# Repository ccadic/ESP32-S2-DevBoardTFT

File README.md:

# ESP32-S2-DevBoardTFT

BREAKING NEWS !!!!! We started a Crowdsupply campaign because of many requests. You can get a fully assembled product here: https://www.crowdsupply.com/morpheans/morphesp-240

Esp32-S2 dev board with 240x240 IPS display

A powerfull dev board with the ESPRESSIF™ ESP32-S2®, a high resolution display, a RGB LED, a battery charger and a bunch of GPIOs.

There are many ESP32 board on the market but very few with the new ESP32-S2 which handles USB communications, new cryptography functions. We wanted to have a board with a built in hi-resolution IPS Color Display. After years playing with previous versions of the ESP32, building security devices, text pagers, we just wanted to go one step further and have our opensource circuit.

We wanted to have something minimalistic but expandable so we chose the ESP32 S2 WROOM component , a classic WS2812B RGB LED, a classic 5v to 3.V voltage regulator. 
We wanted something extremely easy to use therefore fully compatible with ARDUINO® IDE plateform.  We also wanted something simple to handle as a first crowdfunding project. 

Features & Specifications

•	Processing:
    o	32-bit esp32 processor operating at 240 MHz
    o	4 MB SPI flash

•	Wireless:
    o	2.4 GHz Wi-Fi - 802.11b/g/n
    o	PCB Antenna

•	Power:
    o	3.3 V LDO regulator
    o	Optimised power path for low-power battery usage
    o	LiPo battery management
    o	Battery pads on the bottom support both JST PH 
    o	Power LEDs

•	Form-factor:
    o	1.27 pinout spacing connector
    o	Breadboard friendly with the dev shield

•	Connectivity:
    o	GPIO broken out to standard pitch headers 1.27 mm
    o	USB + serial/UART for programming
    o	On Board Programmable RGB LED

•	Control:
    o	Arduino IDE compatibility and MicroPython compatibilité
    o	Supports Arduino IDE
    o	Supports Espressif IDF
    o	Thousands of code over the internet

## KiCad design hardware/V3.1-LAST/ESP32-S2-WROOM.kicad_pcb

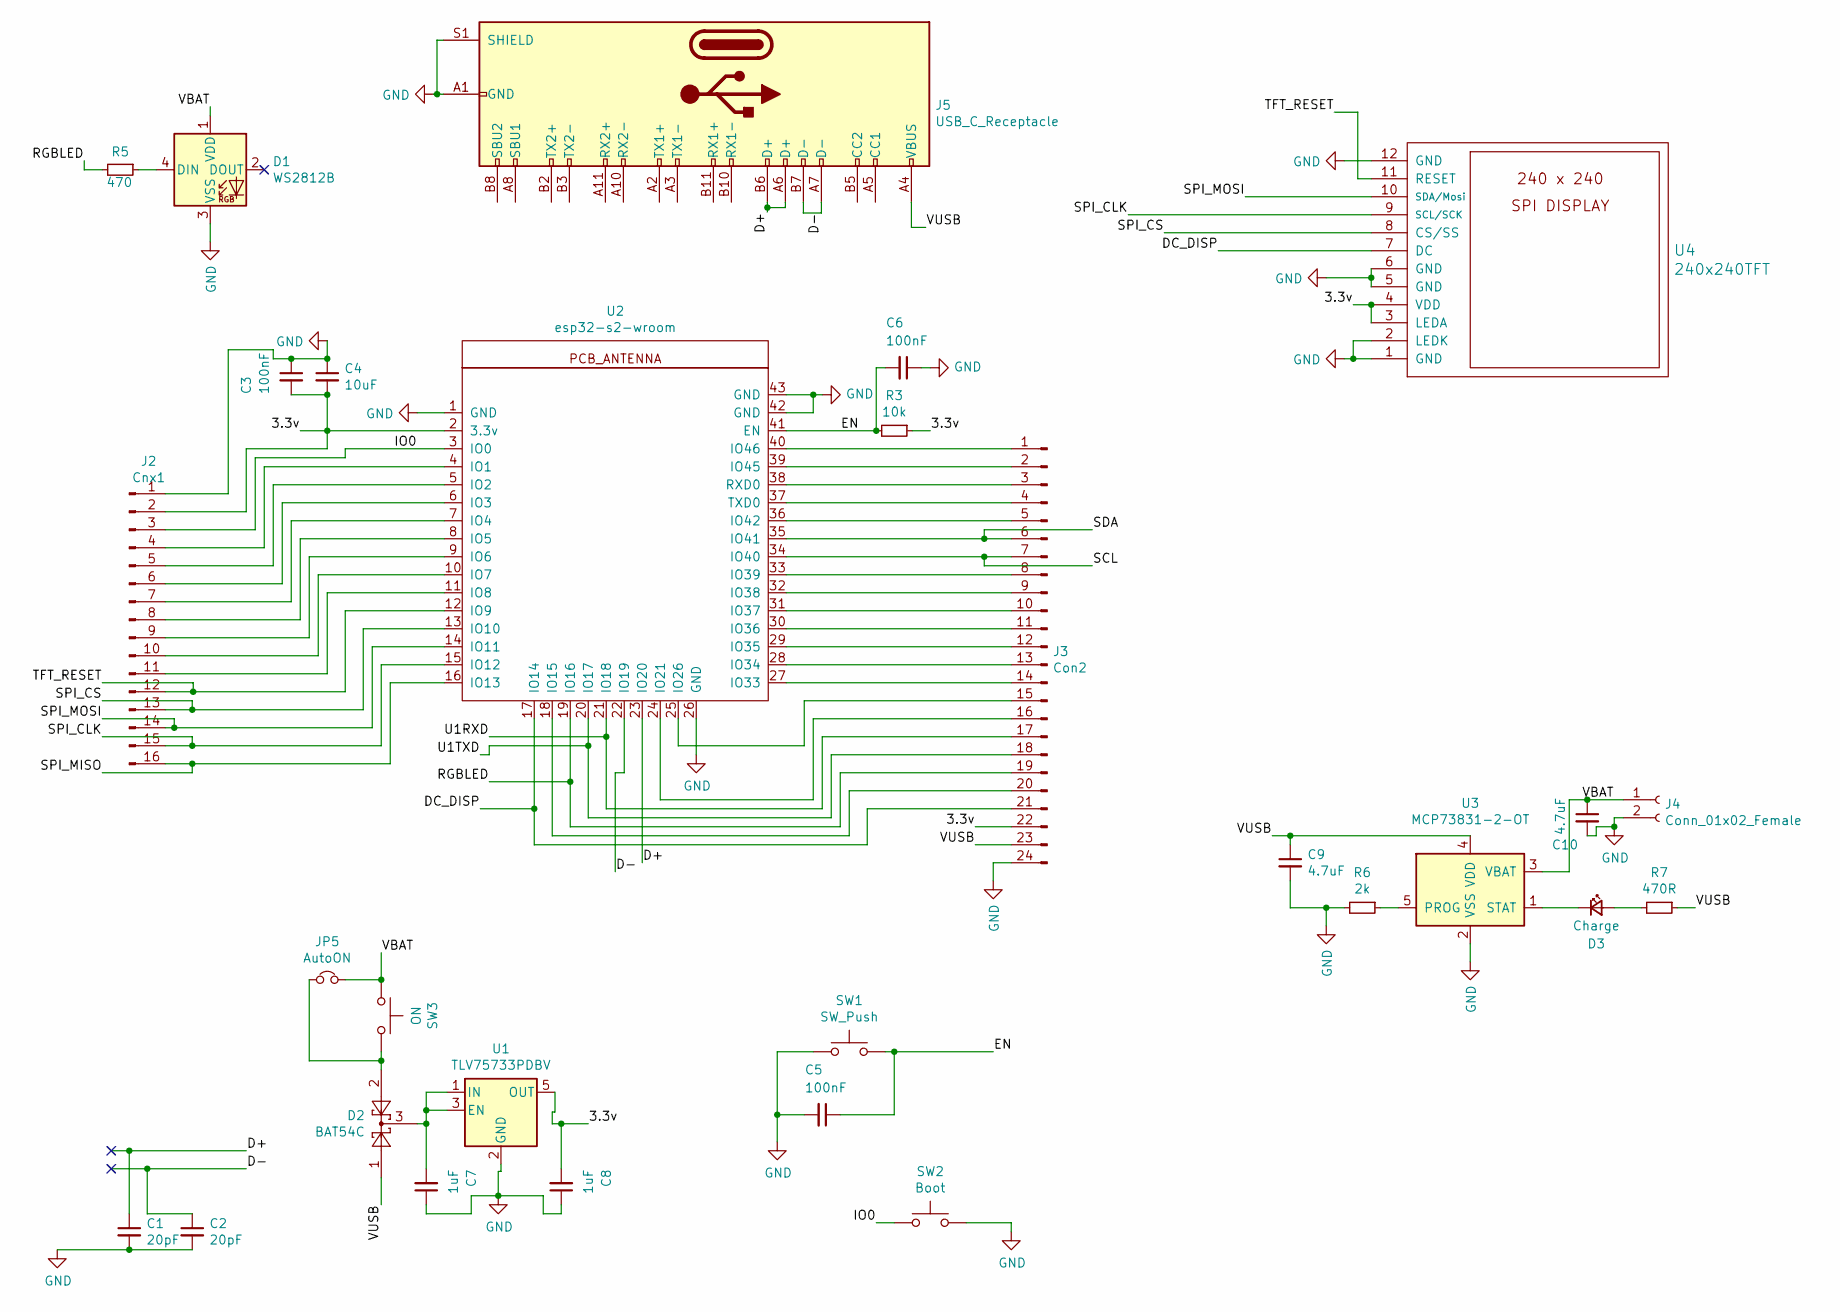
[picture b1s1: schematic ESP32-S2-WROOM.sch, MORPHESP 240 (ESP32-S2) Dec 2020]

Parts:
C1, C2: 20pF; C_0603
C3, C5, C6: 100nF; C_0603
C4: 10uF; C_0603
C7, C8: 1uF; C_0603
C9, C10: 4.7uF; C_0603
D1: WS2812B; LED_WS2812B-PLCC4
D2: BAT54C; SOT-23
D3: Charge; LED_0603
J2: Cnx1; Socket_Strip_Straight_1x16_Pitch1.27mm
J3: Con2; Socket_Strip_Straight_1x24_Pitch1.27mm
J4: Conn_01x02_Female; JST_PH_S2B-PH-SM4-TB_02x2.00mm_Angled
J5: USB_C_Receptacle; USB_C_Receptacle_GT-USB-7010
JP5: AutoON; JumperSmall
R3: 10k; R_0603
R5: 470; R_0603
R6: 2k; R_0603
R7: 470R; R_0603
SW1: SW_Push; SW_SPST_B3U-1000P
SW2: Boot; SW_SPST_B3U-1000P
SW3: ON; SW_SPDT_PCM12
U1: TLV75733PDBV; SOT-23-5
U2: esp32-s2-wroom; esp32-s2-wrooom
U3: MCP73831-2-OT; SOT-23-5
U4: 240x240TFT; 240240TFT

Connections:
/3.3v: C3.2, C4.2, C8.2, J2.2, J3.22, R3.1, U1.5 (OUT), U2.2 (3.3v), U4.3 (LEDA), U4.4 (VDD)
/D+: C1.1, J5.A6 (D+), J5.B6 (D+), U2.23 (IO20)
/D-: C2.1, J5.A7 (D-), J5.B7 (D-), U2.22 (IO19)
/DC_DISP: J3.21, U2.17 (IO14), U4.7 (DC)
/EN: C5.1, C6.2, R3.2, SW1.2, U2.41 (EN)
/IO0: J2.3, SW2.1, U2.3 (IO0)
/RGBLED: J3.19, R5.2, U2.19 (IO16)
/SCL: J3.7, U2.34 (IO40)
/SDA: J3.6, U2.35 (IO41)
/SPI_CLK: J2.15, U2.15 (IO12), U4.9 (SCL/SCK)
/SPI_CS: J2.13, U2.13 (IO10), U4.8 (CS/SS)
/SPI_MISO: J2.16, U2.16 (IO13)
/SPI_MOSI: J2.14, U2.14 (IO11), U4.10 (SDA/Mosi)
/TFT_RESET: J2.12, U2.12 (IO9), U4.11 (RESET)
/U1RXD: J3.17, U2.21 (IO18)
/U1TXD: J3.18, U2.20 (IO17)
/VBAT: C10.1, D1.1 (VDD), J4.1, JP5.2, SW3.1, U3.3 (VBAT)
/VUSB: C9.1, D2.1, J3.23, J5.A4 (VBUS), J5.A9 (VBUS), J5.B4 (VBUS), J5.B9 (VBUS), R7.1, U3.4 (VDD)
GND: C1.2, C2.2, C3.1, C4.1, C5.2, C6.1, C7.1, C8.1, C9.2, C10.2, D1.3 (VSS), J2.1, J3.24, J4.2, J5.A1 (GND), J5.A12 (GND), J5.B1 (GND), J5.B12 (GND), J5.S1 (SHIELD), R6.2, SW1.1, SW2.2, U1.2 (GND), U2.1 (GND), U2.26 (GND), U2.42 (GND), U2.43 (GND), U3.2 (VSS), U4.1 (GND), U4.2 (LEDK), U4.5 (GND), U4.6 (GND), U4.12 (GND)
unnamed: C7.2, D2.3, U1.1 (IN), U1.3 (EN)
unnamed: D1.4 (DIN), R5.1
unnamed: D2.2, JP5.1, SW3.2
unnamed: D3.1 (K), U3.1 (STAT)
unnamed: D3.2 (A), R7.2
unnamed: J2.4, U2.4 (IO1)
unnamed: J2.5, U2.5 (IO2)
unnamed: J2.6, U2.6 (IO3)
unnamed: J2.7, U2.7 (IO4)
unnamed: J2.8, U2.8 (IO5)
unnamed: J2.9, U2.9 (IO6)
unnamed: J2.10, U2.10 (IO7)
unnamed: J2.11, U2.11 (IO8)
unnamed: J3.1, U2.40 (IO46)
unnamed: J3.2, U2.39 (IO45)
unnamed: J3.3, U2.38 (RXD0)
unnamed: J3.4, U2.37 (TXD0)
unnamed: J3.5, U2.36 (IO42)
unnamed: J3.8, U2.33 (IO39)
unnamed: J3.9, U2.32 (IO38)
unnamed: J3.10, U2.31 (IO37)
unnamed: J3.11, U2.30 (IO36)
unnamed: J3.12, U2.29 (IO35)
unnamed: J3.13, U2.28 (IO34)
unnamed: J3.14, U2.27 (IO33)
unnamed: J3.15, U2.25 (IO26)
unnamed: J3.16, U2.24 (IO21)
unnamed: J3.20, U2.18 (IO15)
unnamed: R6.1, U3.5 (PROG)

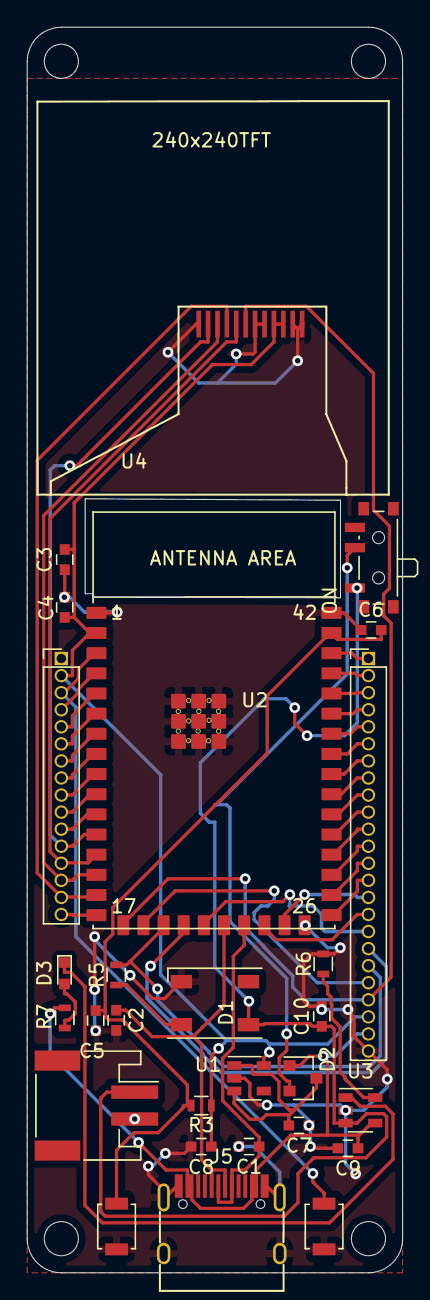
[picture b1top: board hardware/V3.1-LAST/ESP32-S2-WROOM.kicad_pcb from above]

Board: 2 copper layers, 27.9 x 92.7 mm, 29 parts (1 on the bottom side), 48 nets.

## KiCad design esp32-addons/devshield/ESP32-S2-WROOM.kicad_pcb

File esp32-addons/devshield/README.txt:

(C) 2020 - Dr CADIC Philippe
www.morpheans.com

This is a breadboard friendly development shield for the MORPHESP 240
You get access to all GPIO, grouped connectors (SPI , I2C)...

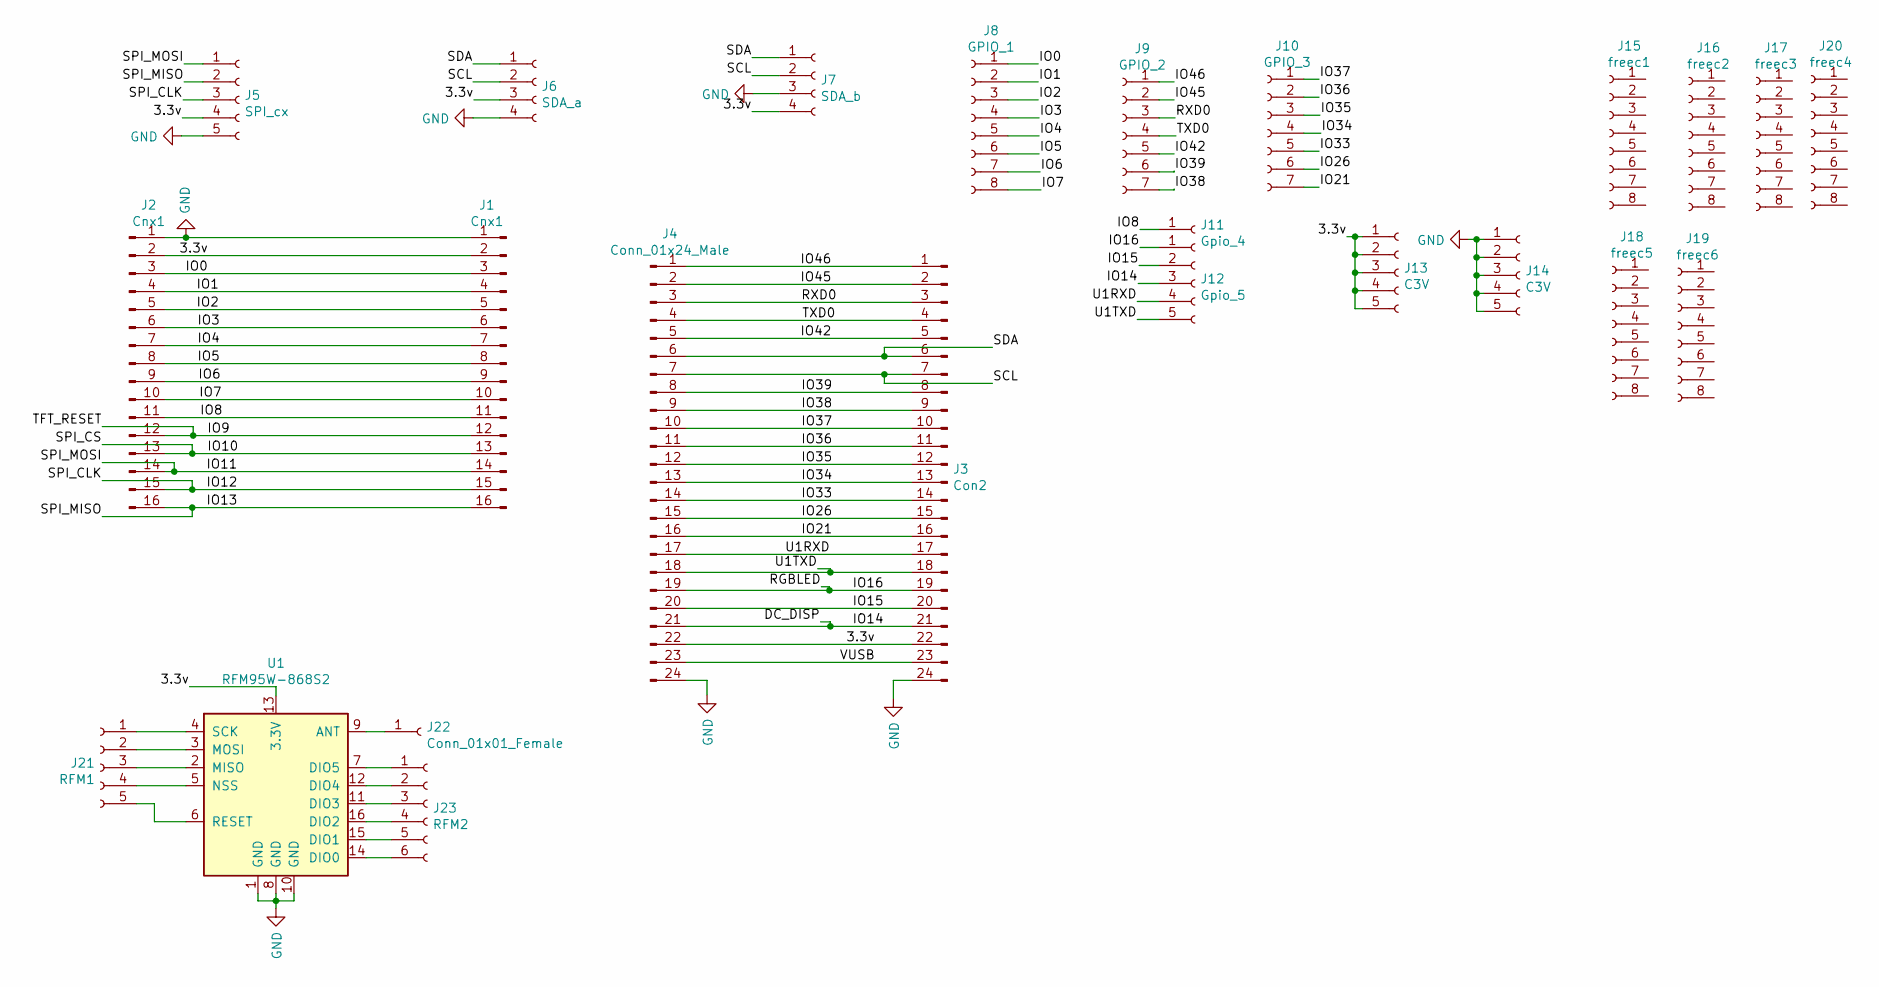
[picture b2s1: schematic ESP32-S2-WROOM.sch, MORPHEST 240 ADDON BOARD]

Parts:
J1: Cnx1; PinSocket_1x16_P2.54mm_Vertical
J2: Cnx1; Socket_Strip_Straight_1x16_Pitch1.27mm
J3: Con2; Socket_Strip_Straight_1x24_Pitch1.27mm
J4: Conn_01x24_Male; PinSocket_1x24_P2.54mm_Vertical
J5: SPI_cx; PinSocket_1x05_P2.54mm_Vertical
J6: SDA_a; PinSocket_1x04_P2.54mm_Vertical
J7: SDA_b; PinSocket_1x04_P2.54mm_Vertical
J8: GPIO_1; PinSocket_1x08_P2.54mm_Vertical
J9: GPIO_2; PinSocket_1x07_P2.54mm_Vertical
J10: GPIO_3; PinSocket_1x07_P2.54mm_Vertical
J11: Gpio_4; PinSocket_1x01_P2.54mm_Vertical
J12: Gpio_5; PinSocket_1x05_P2.54mm_Vertical
J13, J14: C3V; PinSocket_1x05_P2.54mm_Vertical
J15: freec1; PinSocket_1x08_P2.54mm_Vertical
J16: freec2; PinSocket_1x08_P2.54mm_Vertical
J17: freec3; PinSocket_1x08_P2.54mm_Vertical
J18: freec5; PinSocket_1x08_P2.54mm_Vertical
J19: freec6; PinSocket_1x08_P2.54mm_Vertical
J20: freec4; PinSocket_1x08_P2.54mm_Vertical
J21: RFM1; PinSocket_1x05_P2.54mm_Vertical
J22: Conn_01x01_Female; Texas_SWRA416_868MHz_915MHz
J23: RFM2; PinHeader_1x06_P2.54mm_Vertical
U1: RFM95W-868S2; RFM95W_long

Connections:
/3.3v: J1.2, J2.2, J3.22, J4.22, J5.4, J6.3, J7.4, J13.1, J13.2, J13.3, J13.4, J13.5, U1.13 (3.3V)
/DC_DISP: J3.21, J4.21, J12.3
/IO0: J1.3, J2.3, J8.1
/IO1: J1.4, J2.4, J8.2
/IO2: J1.5, J2.5, J8.3
/IO3: J1.6, J2.6, J8.4
/IO4: J1.7, J2.7, J8.5
/IO5: J1.8, J2.8, J8.6
/IO6: J1.9, J2.9, J8.7
/IO7: J1.10, J2.10, J8.8
/IO8: J1.11, J2.11, J11.1
/IO9: J1.12, J2.12
/IO10: J1.13, J2.13
/IO11: J1.14, J2.14, J5.1
/IO12: J1.15, J2.15, J5.3
/IO13: J1.16, J2.16, J5.2
/IO15: J3.20, J4.20, J12.2
/IO16: J3.19, J4.19, J12.1
/IO21: J3.16, J4.16, J10.7
/IO26: J3.15, J4.15, J10.6
/IO33: J3.14, J4.14, J10.5
/IO34: J3.13, J4.13, J10.4
/IO35: J3.12, J4.12, J10.3
/IO36: J3.11, J4.11, J10.2
/IO37: J3.10, J4.10, J10.1
/IO38: J3.9, J4.9, J9.7
/IO39: J3.8, J4.8, J9.6
/IO42: J3.5, J4.5, J9.5
/IO45: J3.2, J4.2, J9.2
/IO46: J3.1, J4.1, J9.1
/RXD0: J3.3, J4.3, J9.3
/SCL: J3.7, J4.7, J6.2, J7.2
/SDA: J3.6, J4.6, J6.1, J7.1
/TXD0: J3.4, J4.4, J9.4
/U1RXD: J3.17, J4.17, J12.4
/U1TXD: J3.18, J4.18, J12.5
/VUSB: J3.23, J4.23
GND: J1.1, J2.1, J3.24, J4.24, J5.5, J6.4, J7.3, J14.1, J14.2, J14.3, J14.4, J14.5, U1.1 (GND), U1.8 (GND), U1.10 (GND)
unnamed: J21.1, U1.4 (SCK)
unnamed: J21.2, U1.3 (MOSI)
unnamed: J21.3, U1.2 (MISO)
unnamed: J21.4, U1.5 (NSS)
unnamed: J21.5, U1.6 (RESET)
unnamed 43: J22.1, U1.9 (ANT); also elsewhere on the board
unnamed: J23.1, U1.7 (DIO5)
unnamed: J23.2, U1.12 (DIO4)
unnamed: J23.3, U1.11 (DIO3)
unnamed: J23.4, U1.16 (DIO2)
unnamed: J23.5, U1.15 (DIO1)
unnamed: J23.6, U1.14 (DIO0)

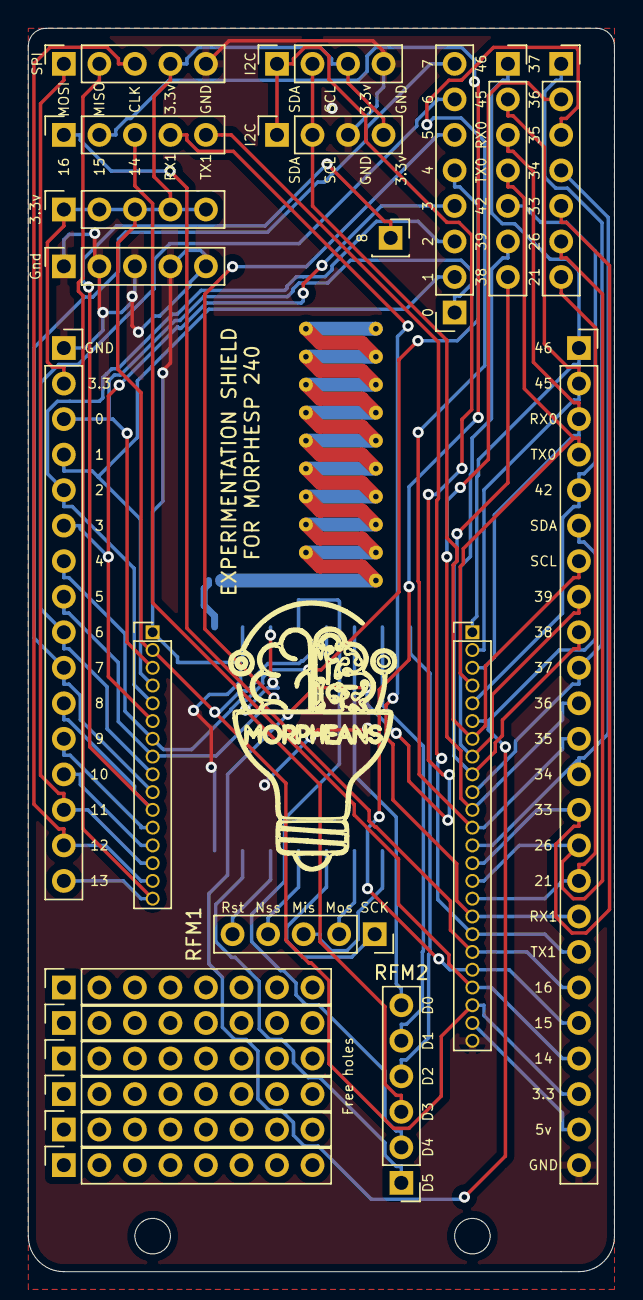
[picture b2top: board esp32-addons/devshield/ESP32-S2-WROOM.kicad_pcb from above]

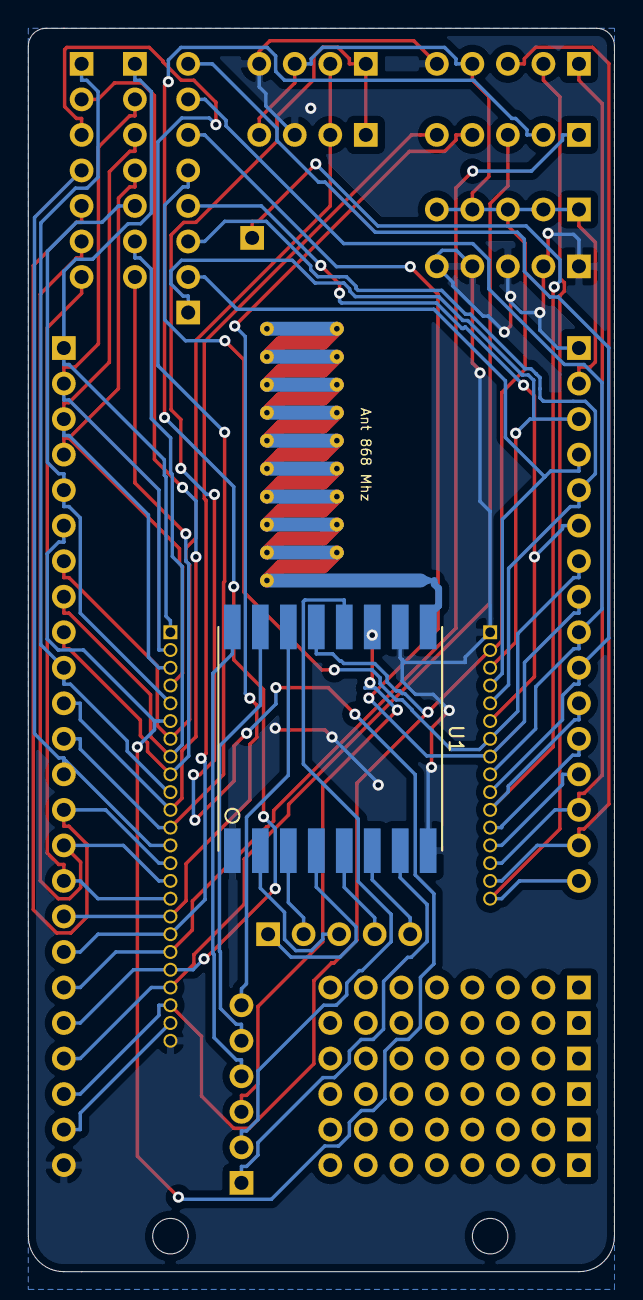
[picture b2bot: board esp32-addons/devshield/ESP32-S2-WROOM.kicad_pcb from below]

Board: 2 copper layers, 41.9 x 88.9 mm, 24 parts (2 on the bottom side), 50 nets.

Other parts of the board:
Ant 868 Mhz: Conn_01x01_Female; Texas_SWRA416_868MHz_915MHz

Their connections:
unnamed 43: Ant 868 Mhz.1; also elsewhere on the board
